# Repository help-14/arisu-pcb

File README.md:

# Arisu Keyboard PCB
アリス PCB designed using KiCad. The layout is inspired by Lyn's EM7 and TGR Alice with some modification of my own.

This Fork version change Micro USB to Mini USB.

Key differences:
- I removed the extra [B] key on the right half and shifted the [NM,.?] row to the left by 0.25U.
- Shifted the 3 keys to the right and added arrow keys.
- Tweaked the bottom so that the 1.5U keys doesn't protrude out a little.

Shifting the [NM,.?] row to the left by 0.25U required quite some work on the arrangement of keys for the right half.
As a result, this does not give the same typing experience as Lyn's EM7 and TGR Alice.
Lyn's EM7 and TGR Alice uses the home row as the center point to vertically align both halves while I used the number row instead.
Due to the nature of staggered keyboards, aligning using the number row resulted in the home row not being aligned.

Disclaimer: Use these files at your own risk.

## Gerber Files
Download the gerber files under [releases](https://github.com/FateNozomi/arisu-pcb/releases).

## Assembly
For the components required, you may refer to the bill of materials included along with the release as reference or load up the design file in KiCad.
All the components can be soldered using a regular soldering iron, though soldering the Micro USB receptacle might be the biggest hurdle.

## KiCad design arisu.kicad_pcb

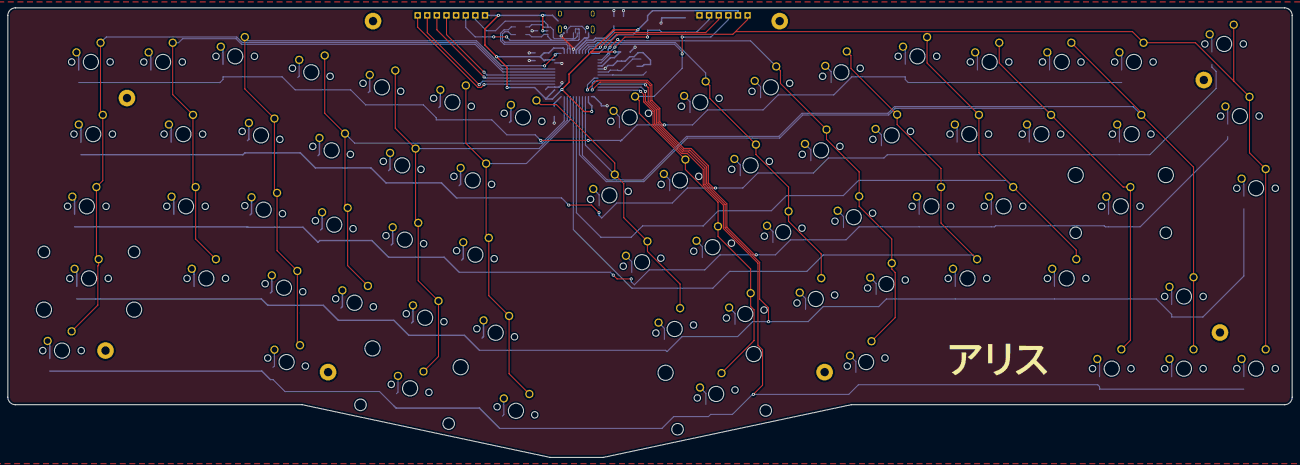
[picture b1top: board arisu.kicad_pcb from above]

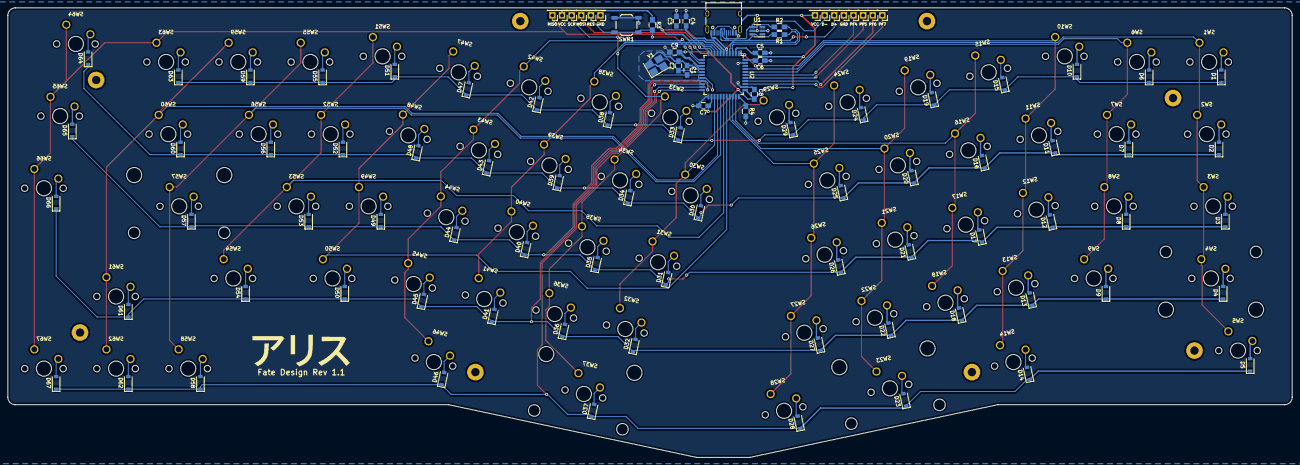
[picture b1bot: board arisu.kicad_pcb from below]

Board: 2 copper layers, 339.1 x 118.7 mm, 173 parts (98 on the bottom side), 101 nets.

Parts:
C1, C2: 22pF; C_0805_HandSoldering
C3: 10uF; C_0805_HandSoldering
C4: 1uF (±10%); C_0805_HandSoldering
C5: 1uF; C_0805_HandSoldering
C6, C7, C8, C9: 0.1uF; C_0805_HandSoldering
D1, D2, D3, D4, D5, D6, D7, D8, D9, D10, D11, D12, D13, D14, D15, D16, D17, D18, D19, D20, D21, D22, D23, D24, D25, D26, D27, D28, D29, D30, D31, D32, D33, D34, D35, D36, D37, D38, D39, D40, D41, D42, D43, D44, D45, D46, D47, D48, D49, D50, D51, D52, D53, D54, D55, D56, D57, D58, D59, D60, D61, D62, D63, D64, D65, D66, D67: D; D_SOD-123
D+: D+; Pin_Header_Straight_1x01_Pitch2.54mm
D-: D-; Pin_Header_Straight_1x01_Pitch2.54mm
GND: GND; Pin_Header_Straight_1x01_Pitch2.54mm
GND#2: GND; Pin_Header_Straight_1x01_Pitch2.54mm
H1, H2, H3, H4, H5, H6, H7, H8: MountingHole; MountingHole_2.2mm_M2_Pad
MISO: MISO; Pin_Header_Straight_1x01_Pitch2.54mm
MOSI: MOSI; Pin_Header_Straight_1x01_Pitch2.54mm
PF4: PF4; Pin_Header_Straight_1x01_Pitch2.54mm
PF5: PF5; Pin_Header_Straight_1x01_Pitch2.54mm
PF6: PF6; Pin_Header_Straight_1x01_Pitch2.54mm
PF7: PF7; Pin_Header_Straight_1x01_Pitch2.54mm
R1, R2: 22; R_0805_HandSoldering
R3, R4: 10K; R_0805_HandSoldering
RES: RES; Pin_Header_Straight_1x01_Pitch2.54mm
SCK: SCK; Pin_Header_Straight_1x01_Pitch2.54mm
SW1, SW6, SW7, SW8, SW9, SW10, SW11, SW12, SW13, SW15, SW16, SW17, SW18, SW19, SW20, SW21, SW22, SW24, SW25, SW26, SW27, SW28, SW29, SW30, SW31, SW32, SW33, SW34, SW35, SW36, SW38, SW39, SW40, SW41, SW42, SW43, SW44, SW45, SW47, SW48, SW49, SW50, SW51, SW52, SW53, SW55, SW56, SW58, SW59, SW61, SW62, SW63, SW64, SW65, SW66, SW67: SW_Push; SW_Cherry_MX_1.00u_PCB
SW2, SW5, SW14, SW46, SW60: SW_Push; SW_Cherry_MX_1.50u_PCB
SW3, SW54: SW_Push; SW_Cherry_MX_1.75u_PCB
SW4: SW_Push; SW_Cherry_MX_2.25u_PCB
SW23: SW_Push; SW_Cherry_MX_2.00u_PCB_ReversedStabilizers
SW37: SW_Push; SW_Cherry_MX_2.75u_PCB_ReversedStabilizers
SW57: SW_Push; SW_Cherry_MX_2.25u_PCB_ReversedStabilizers
SWR1: SW_Push; SW_SPST_TL3342
U1: USBLC6-2SC6; SOT-23-6_Handsoldering
U2: ATmega32U4-AU; TQFP-44_10x10mm_Pitch0.8mm
VCC: VCC; Pin_Header_Straight_1x01_Pitch2.54mm
VCC#2: VCC; Pin_Header_Straight_1x01_Pitch2.54mm
Y1: Crystal_GND24; Crystal_SMD_SeikoEpson_FA238-4pin_3.2x2.5mm_HandSoldering

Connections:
/MISO: MISO.1, SW63.1, SW64.1, SW65.1, SW66.1, SW67.1, U2.11
/MOSI: MOSI.1, U2.10
/PF4: PF4.1, U2.39
/PF5: PF5.1, U2.38
/PF6: PF6.1, U2.37
/PF7: PF7.1, U2.36
/SCK: SCK.1, SW33.1, SW34.1, SW35.1, SW36.1, SW37.1, U2.9
/col0: SW1.1, SW2.1, SW3.1, SW4.1, SW5.1, U2.41
/col1: SW6.1, SW7.1, SW8.1, SW9.1, U2.40
/col2: SW10.1, SW11.1, SW12.1, SW13.1, SW14.1, U2.1
/col3: SW15.1, SW16.1, SW17.1, SW18.1, U2.32
/col4: SW19.1, SW20.1, SW21.1, SW22.1, SW23.1, U2.31
/col5: SW24.1, SW25.1, SW26.1, SW27.1, SW28.1, U2.30
/col6: SW29.1, SW30.1, SW31.1, SW32.1, U2.25
/col8: SW38.1, SW39.1, SW40.1, SW41.1, U2.8
/col9: SW42.1, SW43.1, SW44.1, SW45.1, SW46.1, U2.12
/col10: SW47.1, SW48.1, SW49.1, SW50.1, U2.29
/col11: SW51.1, SW52.1, SW53.1, SW54.1, U2.28
/col12: SW55.1, SW56.1, SW57.1, SW58.1, U2.27
/col13: SW59.1, SW60.1, SW61.1, SW62.1, U2.26
/row0: D1.1, D6.1, D10.1, D15.1, D19.1, D24.1, D29.1, D33.1, D38.1, D42.1, D47.1, D51.1, D55.1, D59.1, D63.1, U2.18
/row1: D2.1, D7.1, D11.1, D16.1, D20.1, D25.1, D30.1, D34.1, D39.1, D43.1, D48.1, D52.1, D56.1, D60.1, D64.1, U2.19
/row2: D3.1, D8.1, D12.1, D17.1, D21.1, D26.1, D31.1, D35.1, D40.1, D44.1, D49.1, D53.1, D57.1, D65.1, U2.20
/row3: D4.1, D9.1, D13.1, D18.1, D22.1, D27.1, D32.1, D36.1, D41.1, D45.1, D50.1, D54.1, D61.1, D66.1, U2.21
/row4: D5.1, D14.1, D23.1, D28.1, D37.1, D46.1, D58.1, D62.1, D67.1, U2.22
/~RES~: R3.2, RES.1, SWR1.2, U2.13
D+: D+.1, R1.1, R1.2, U1.6, U2.4
D-: D-.1, R2.1, R2.2, U1.4, U2.3
GND: C1.1, C2.2, C3.2, C4.2, C5.2, C6.2, C7.2, C8.2, C9.2, GND.1, GND#2.1, R4.2, SWR1.1, U1.2, U2.5, U2.15, U2.23, U2.35, U2.43, Y1.2, Y1.4
unnamed: C4.1, U2.6
unnamed: D1.2, SW1.2
unnamed: D2.2, SW2.2
unnamed: D3.2, SW3.2
unnamed: D4.2, SW4.2
unnamed: D5.2, SW5.2
unnamed: D6.2, SW6.2
unnamed: D7.2, SW7.2
unnamed: D8.2, SW8.2
unnamed: D9.2, SW9.2
unnamed: D10.2, SW10.2
unnamed: D11.2, SW11.2
unnamed: D12.2, SW12.2
unnamed: D13.2, SW13.2
unnamed: D14.2, SW14.2
unnamed: D15.2, SW15.2
unnamed: D16.2, SW16.2
unnamed: D17.2, SW17.2
unnamed: D18.2, SW18.2
unnamed: D19.2, SW19.2
unnamed: D20.2, SW20.2
unnamed: D21.2, SW21.2
unnamed: D22.2, SW22.2
unnamed: D23.2, SW23.2
unnamed: D24.2, SW24.2
unnamed: D25.2, SW25.2
unnamed: D26.2, SW26.2
unnamed: D27.2, SW27.2
unnamed: D28.2, SW28.2
unnamed: D29.2, SW29.2
unnamed: D30.2, SW30.2
unnamed: D31.2, SW31.2
unnamed: D32.2, SW32.2
unnamed: D33.2, SW33.2
unnamed: D34.2, SW34.2
unnamed: D35.2, SW35.2
unnamed: D36.2, SW36.2
unnamed: D37.2, SW37.2
unnamed: D38.2, SW38.2
unnamed: D39.2, SW39.2
unnamed: D40.2, SW40.2
unnamed: D41.2, SW41.2
unnamed: D42.2, SW42.2
unnamed: D43.2, SW43.2
unnamed: D44.2, SW44.2
unnamed: D45.2, SW45.2
unnamed: D46.2, SW46.2
unnamed: D47.2, SW47.2
unnamed: D48.2, SW48.2
unnamed: D49.2, SW49.2
unnamed: D50.2, SW50.2
unnamed: D51.2, SW51.2
unnamed: D52.2, SW52.2
unnamed: D53.2, SW53.2
unnamed: D54.2, SW54.2
unnamed: D55.2, SW55.2
unnamed: D56.2, SW56.2
unnamed: D57.2, SW57.2
unnamed: D58.2, SW58.2
unnamed: D59.2, SW59.2
unnamed: D60.2, SW60.2
unnamed: D61.2, SW61.2
unnamed: D62.2, SW62.2
unnamed: D63.2, SW63.2
unnamed: D64.2, SW64.2
unnamed: D65.2, SW65.2
unnamed: D66.2, SW66.2
unnamed: D67.2, SW67.2
unnamed: R4.1, U2.33
VCC: C3.1, C5.1, C6.1, C7.1, C8.1, C9.1, R3.1, U1.5, U2.2, U2.7, U2.14, U2.24, U2.34, U2.44, VCC.1, VCC#2.1
XTAL1: C1.2, U2.17, Y1.1
XTAL2: C2.1, U2.16, Y1.3

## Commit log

2020-04-11 change micro usb to mini usb
2020-10-24 v2.0 with usb c
